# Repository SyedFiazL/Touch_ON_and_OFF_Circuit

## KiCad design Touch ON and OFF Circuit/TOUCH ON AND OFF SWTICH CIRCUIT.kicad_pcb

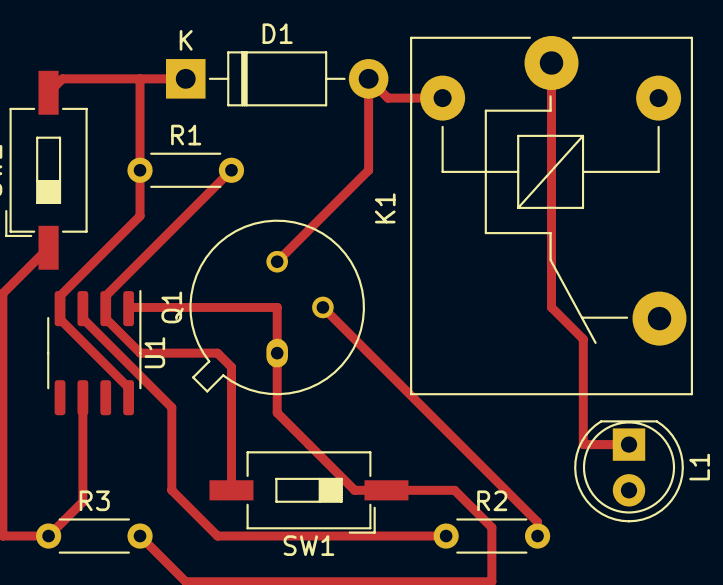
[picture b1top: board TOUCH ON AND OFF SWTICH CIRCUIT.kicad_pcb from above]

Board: 2 copper layers, 10 parts (0 on the bottom side), 8 nets.

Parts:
D1: 1N4007; D_DO-41_SOD81_P10.16mm_Horizontal
K1: DIPxx-1Cxx-51x; Relay_SPST_SANYOU_SRD_Series_Form_B
L1: LD271; LED_D5.0mm_IRGrey
Q1: 2N2219; TO-39-3
R1: 3.3M; R_Axial_DIN0204_L3.6mm_D1.6mm_P5.08mm_Horizontal
R2: 1k; R_Axial_DIN0204_L3.6mm_D1.6mm_P5.08mm_Horizontal
R3: 1M; R_Axial_DIN0204_L3.6mm_D1.6mm_P5.08mm_Horizontal
SW1: switch 1; SW_DIP_SPSTx01_Slide_6.7x4.1mm_W8.61mm_P2.54mm_LowProfile
SW2: switch 2; SW_DIP_SPSTx01_Slide_6.7x4.1mm_W8.61mm_P2.54mm_LowProfile
U1: LM555xM; SOIC-8_3.9x4.9mm_P1.27mm

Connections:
GND: Q1.1 (E), R3.2, SW1.1, U1.1 (GND)
unnamed: D1.2 (A), K1.2, Q1.3 (C)
unnamed: K1.1, L1.1 (K)
unnamed: Q1.2 (B), R2.2
unnamed: R1.2, SW1.2, U1.2 (TR)
unnamed: R2.1, U1.3 (Q)
unnamed: R3.1, SW2.1, U1.6 (THR)
VCC: D1.1 (K), R1.1, SW2.2, U1.4 (R), U1.8 (VCC)
